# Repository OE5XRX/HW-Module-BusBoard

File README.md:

# HW-Module-BusBoard

## License

This project is licensed under [CERN-OHL-S-2.0](https://choosealicense.com/licenses/cern-ohl-s-2.0/).

## Badges

<br>
<br>
<br>
<br>
<br>

## Contact

OE5XRX Amateur Radio Club<br>
🌐 https://oe5xrx.org<br>
✉️ info@oe5xrx.org<br>

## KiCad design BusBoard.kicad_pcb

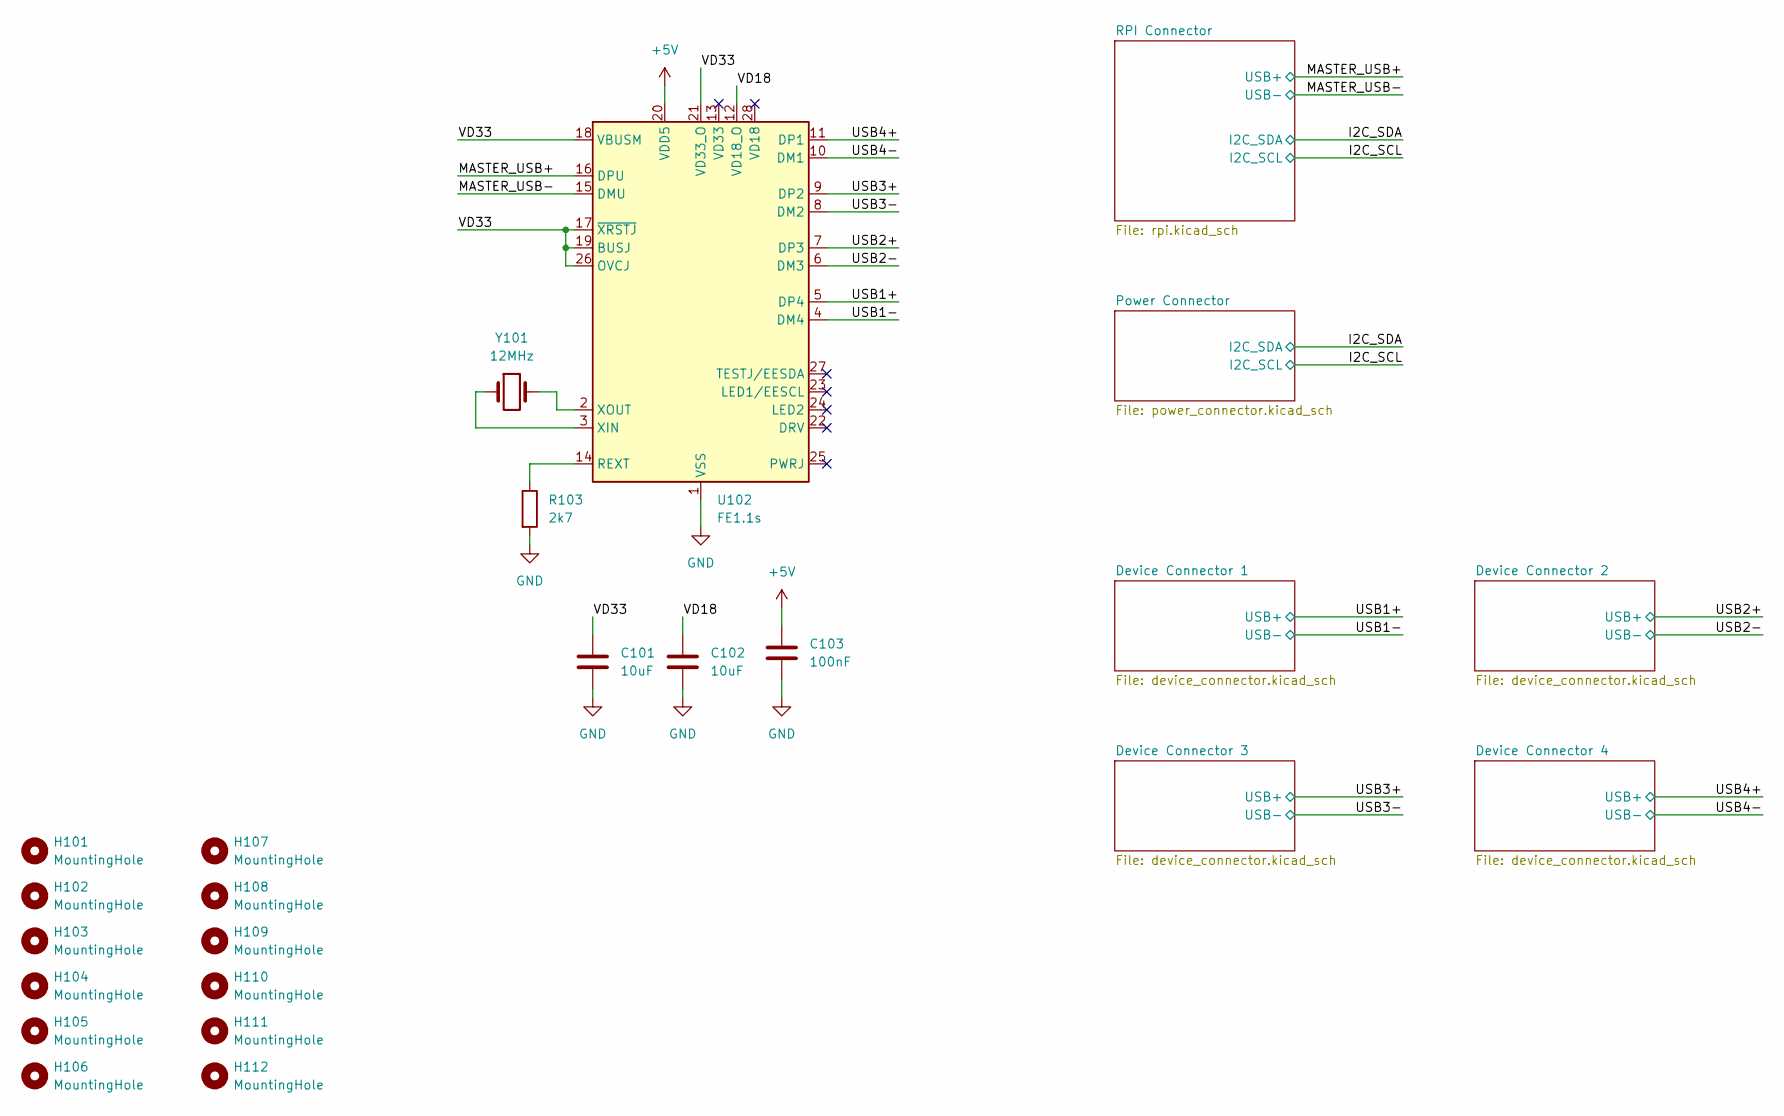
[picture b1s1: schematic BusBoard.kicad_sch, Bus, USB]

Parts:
C101, C102: 10uF; C_0805_2012Metric; LCSC C13585
C103: 100nF; C_0805_2012Metric; LCSC C28233
H101, H102, H103, H104, H105, H106, H107, H108, H109, H110, H111, H112: MountingHole; MountingHole_3.2mm_M3
R103: 2k7; R_0805_2012Metric; LCSC C352230
U102: FE1.1s; SSOP-28_3.9x9.9mm_P0.635mm; LCSC C6706491
Y101: 12MHz; M49S-SMD; LCSC C2983432

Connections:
+5V: C103.1, U102.20 (VDD5); also elsewhere on the board
/MASTER_USB+: U102.16 (DPU); also elsewhere on the board
/MASTER_USB-: U102.15 (DMU); also elsewhere on the board
/USB1+: U102.5 (DP4); also elsewhere on the board
/USB1-: U102.4 (DM4); also elsewhere on the board
/USB2+: U102.7 (DP3); also elsewhere on the board
/USB2-: U102.6 (DM3); also elsewhere on the board
/USB3+: U102.9 (DP2); also elsewhere on the board
/USB3-: U102.8 (DM2); also elsewhere on the board
/USB4+: U102.11 (DP1); also elsewhere on the board
/USB4-: U102.10 (DM1); also elsewhere on the board
/VD18: C102.1, U102.12 (VD18_O)
/VD33: C101.1, U102.17 (~XRSTJ), U102.18 (VBUSM), U102.19 (BUSJ), U102.21 (VD33_O), U102.26 (OVCJ)
GND: C101.2, C102.2, C103.2, R103.2, U102.1 (VSS); also elsewhere on the board
unnamed: R103.1, U102.14 (REXT)
unnamed: U102.3 (XIN), Y101.1
unnamed: U102.2 (XOUT), Y101.2

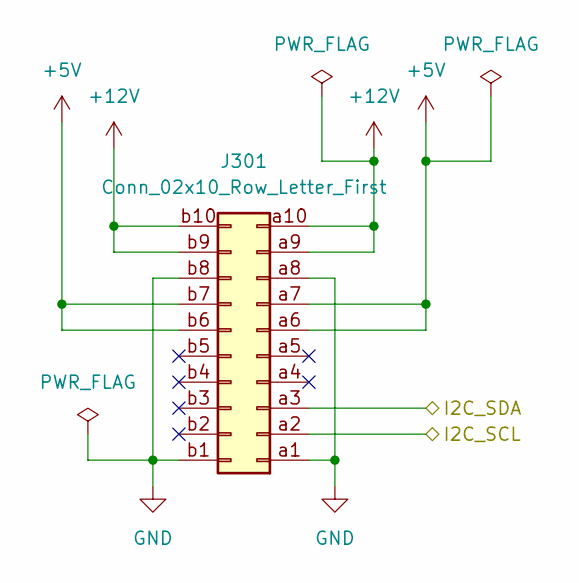
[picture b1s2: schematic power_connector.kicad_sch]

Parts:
J301: Conn_02x10_Row_Letter_First; PCN10-20P-2.54DSA; MOUSER 798-PCN1020P254DSA72

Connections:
+5V: J301.a6, J301.a7, J301.b6, J301.b7; also elsewhere on the board
+12V: J301.a9, J301.a10, J301.b9, J301.b10; also elsewhere on the board
/I2C_SCL: J301.a2; also elsewhere on the board
/I2C_SDA: J301.a3; also elsewhere on the board
GND: J301.a1, J301.a8, J301.b1, J301.b8; also elsewhere on the board

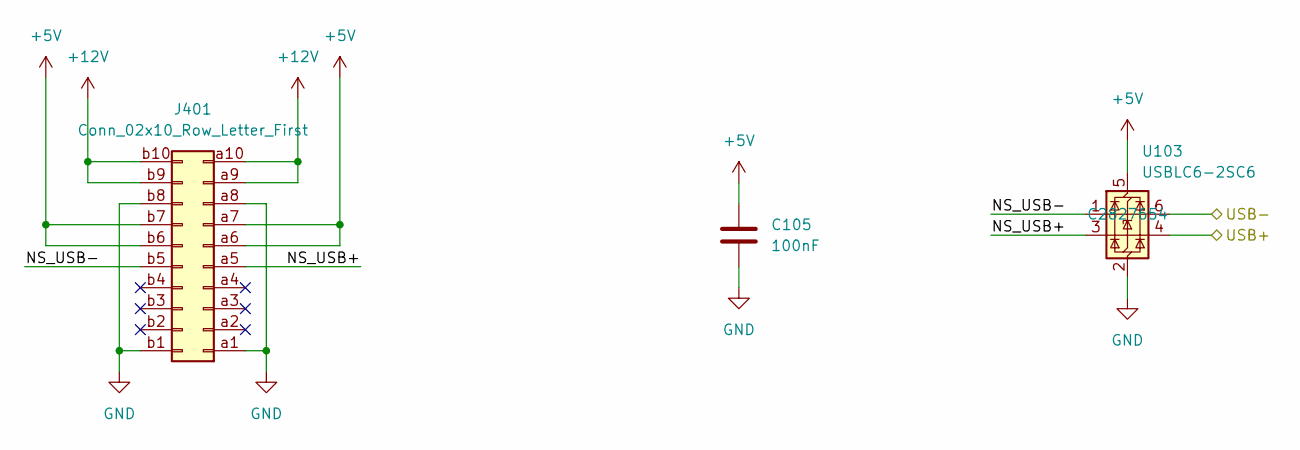
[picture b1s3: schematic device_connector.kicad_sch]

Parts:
C105: 100nF; C_0805_2012Metric; LCSC C28233
J401: Conn_02x10_Row_Letter_First; PCN10-20P-2.54DSA; MOUSER 798-PCN1020P254DSA72
U103: USBLC6-2SC6; SOT-23-6; LCSC C2827654

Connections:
+5V: C105.1, J401.a6, J401.a7, J401.b6, J401.b7, U103.5 (VBUS); also elsewhere on the board
+12V: J401.a9, J401.a10, J401.b9, J401.b10; also elsewhere on the board
/Device Connector 1/NS_USB+: J401.a5, U103.3 (I/O2)
/Device Connector 1/NS_USB-: J401.b5, U103.1 (I/O1)
/USB1+: U103.4 (I/O2); also elsewhere on the board
/USB1-: U103.6 (I/O1); also elsewhere on the board
GND: C105.2, J401.a1, J401.a8, J401.b1, J401.b8, U103.2 (GND); also elsewhere on the board

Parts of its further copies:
C106, C107, C108: 100nF; C_0805_2012Metric; LCSC C28233
J501, J601, J701: Conn_02x10_Row_Letter_First; PCN10-20P-2.54DSA; MOUSER 798-PCN1020P254DSA72
U104, U105, U106: USBLC6-2SC6; SOT-23-6; LCSC C2827654

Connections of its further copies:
+5V: C106.1, C107.1, C108.1, J501.a6, J501.a7, J501.b6, J501.b7, J601.a6, J601.a7, J601.b6, J601.b7, J701.a6, J701.a7, J701.b6, J701.b7, U104.5 (VBUS), U105.5 (VBUS), U106.5 (VBUS); also elsewhere on the board
+12V: J501.a9, J501.a10, J501.b9, J501.b10, J601.a9, J601.a10, J601.b9, J601.b10, J701.a9, J701.a10, J701.b9, J701.b10; also elsewhere on the board
/Device Connector 2/NS_USB+: J501.a5, U104.3 (I/O2)
/Device Connector 2/NS_USB-: J501.b5, U104.1 (I/O1)
/Device Connector 3/NS_USB+: J601.a5, U105.3 (I/O2)
/Device Connector 3/NS_USB-: J601.b5, U105.1 (I/O1)
/Device Connector 4/NS_USB+: J701.a5, U106.3 (I/O2)
/Device Connector 4/NS_USB-: J701.b5, U106.1 (I/O1)
/USB2+: U104.4 (I/O2); also elsewhere on the board
/USB2-: U104.6 (I/O1); also elsewhere on the board
/USB3+: U105.4 (I/O2); also elsewhere on the board
/USB3-: U105.6 (I/O1); also elsewhere on the board
/USB4+: U106.4 (I/O2); also elsewhere on the board
/USB4-: U106.6 (I/O1); also elsewhere on the board
GND: C106.2, C107.2, C108.2, J501.a1, J501.a8, J501.b1, J501.b8, J601.a1, J601.a8, J601.b1, J601.b8, J701.a1, J701.a8, J701.b1, J701.b8, U104.2 (GND), U105.2 (GND), U106.2 (GND); also elsewhere on the board

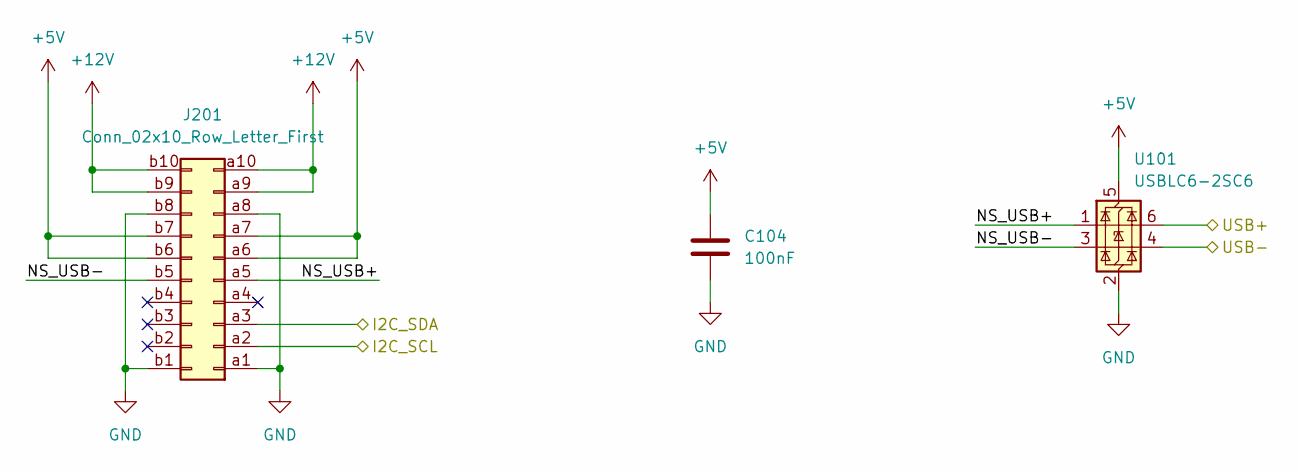
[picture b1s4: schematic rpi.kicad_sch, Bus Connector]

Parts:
C104: 100nF; C_0805_2012Metric; LCSC C28233
J201: Conn_02x10_Row_Letter_First; PCN10-20P-2.54DSA; MOUSER 798-PCN1020P254DSA72
U101: USBLC6-2SC6; SOT-23-6; LCSC C2827654

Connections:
+5V: C104.1, J201.a6, J201.a7, J201.b6, J201.b7, U101.5 (VBUS); also elsewhere on the board
+12V: J201.a9, J201.a10, J201.b9, J201.b10; also elsewhere on the board
/I2C_SCL: J201.a2; also elsewhere on the board
/I2C_SDA: J201.a3; also elsewhere on the board
/MASTER_USB+: U101.6 (I/O1); also elsewhere on the board
/MASTER_USB-: U101.4 (I/O2); also elsewhere on the board
/RPI Connector/NS_USB+: J201.a5, U101.1 (I/O1)
/RPI Connector/NS_USB-: J201.b5, U101.3 (I/O2)
GND: C104.2, J201.a1, J201.a8, J201.b1, J201.b8, U101.2 (GND); also elsewhere on the board

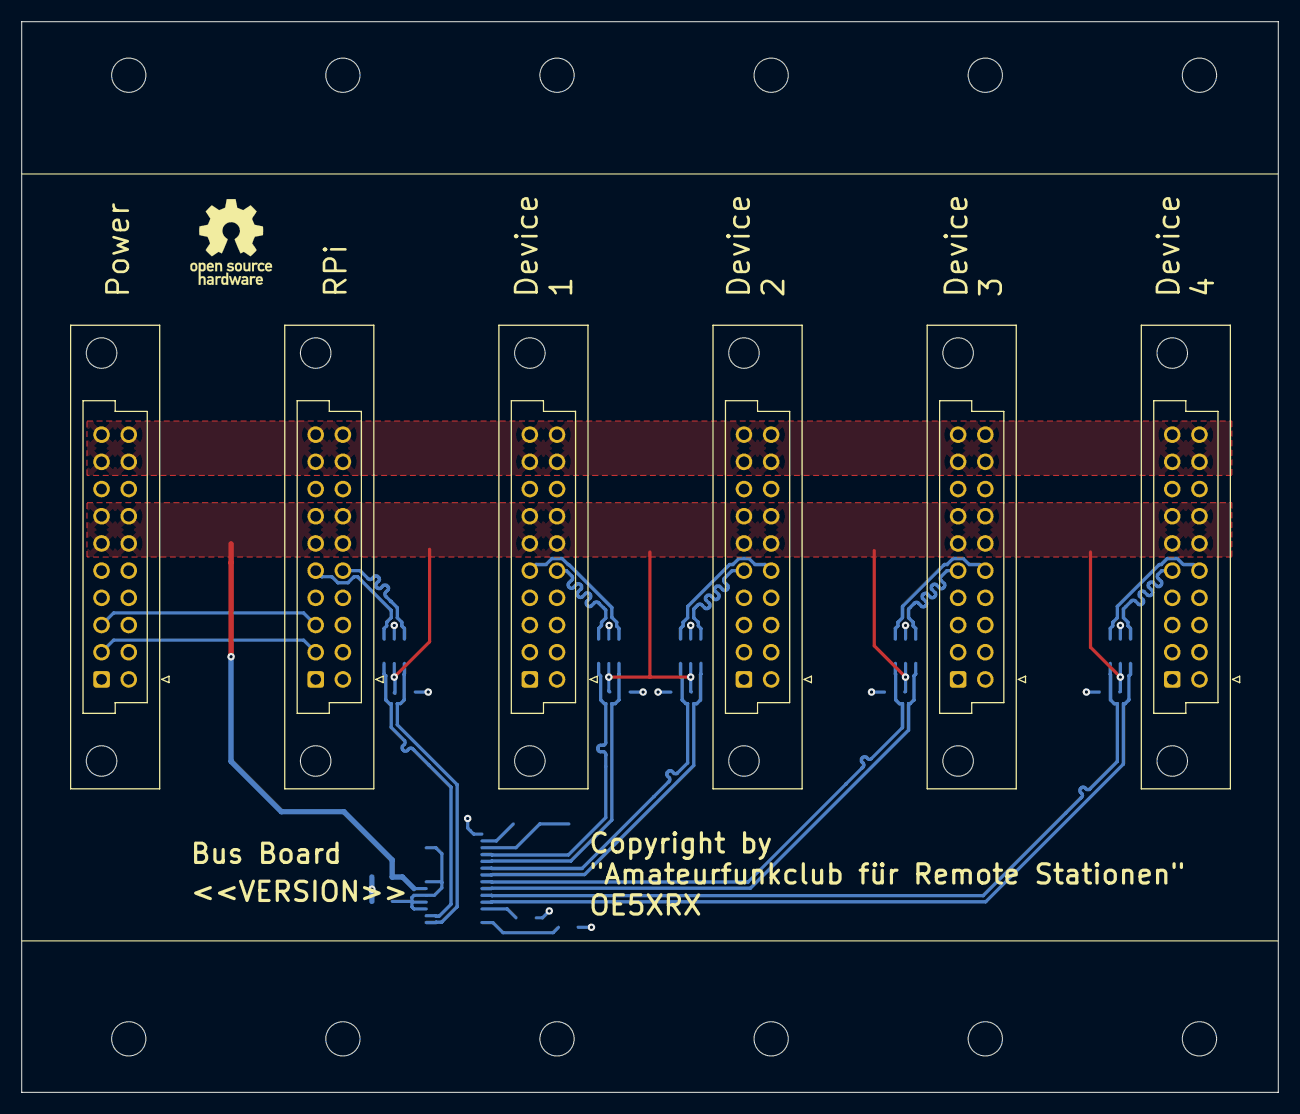
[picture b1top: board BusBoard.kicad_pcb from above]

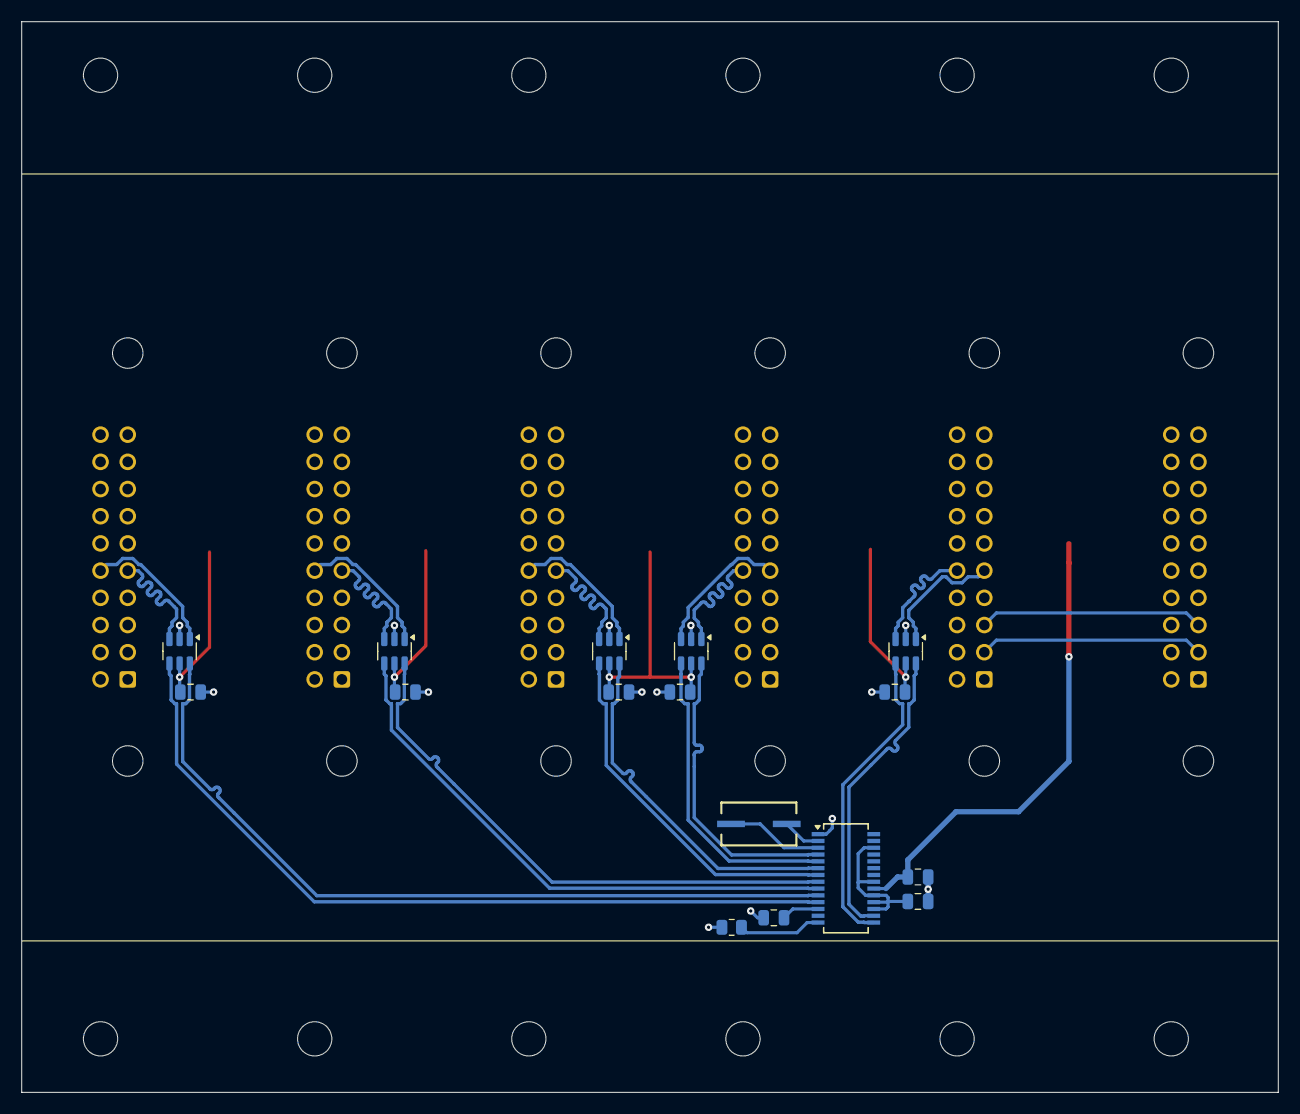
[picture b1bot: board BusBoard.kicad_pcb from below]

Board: 4 copper layers, 117.4 x 100.0 mm, 34 parts (16 on the bottom side), 30 nets.

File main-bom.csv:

Row,Description,Part,References,Value,Footprint,Quantity Per PCB,Status,Datasheet,LCSC,MOUSER
1,Unpolarized capacitor,C,C103 C104 C105 C106 C107 C108,100nF,C_0805_2012Metric,6, ,~,C28233,
2,Unpolarized capacitor,C,C101 C102,10uF,C_0805_2012Metric,2, ,~,C13585,
3,"Generic connector, double row, 02x10, row letter first pin numbering scheme (pin number consists of a letter for the row and a number for the pin index in this row. a1, ..., aN; b1, ..., bN), script generated (kicad-library-utils/schlib/autogen/connector/)",Conn_02x10_Row_Letter_First,J201 J301 J401 J501 J601 J701,Conn_02x10_Row_Letter_First,PCN10-20P-2.54DSA,6, ,~,,798-PCN1020P254DSA72
4,Resistor,R,R103,2k7,R_0805_2012Metric,1, ,~,C352230,
5,"USB 2.0 High Speed 4-Port Hub Controller, SSOP-28",FE1.1s,U102,FE1.1s,SSOP-28_3.9x9.9mm_P0.635mm,1, ,https://cdn-shop.adafruit.com/product-files/2991/FE1.1s+Data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,C6706491,
6,"Very low capacitance ESD protection diode, 2 data-line, SOT-23-6",USBLC6-2SC6,U101 U103 U104 U105 U106,USBLC6-2SC6,SOT-23-6,5, ,https://www.st.com/resource/en/datasheet/usblc6-2.pdf,C2827654,
7,Two pin crystal,Crystal,Y101,12MHz,M49S-SMD,1, ,~,C2983432,

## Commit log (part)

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2025-08-27 setup new project
2025-08-27 fix path
2025-09-05 🔄 synced local '.github/workflows/create-debug-docs.yaml' with remote '.github/workflows/create-debug-docs.yaml'
2025-09-05 🔄 created local 'Gemfile' from remote 'Gemfile'
2025-09-05 🔄 created local 'doc/favicon.ico' from remote 'doc/favicon.ico'
2025-09-05 🔄 created local 'doc/_config.yml' from remote 'doc/_config.yml'
2025-09-05 Initial gh-pages commit
2025-09-05 Deploying to gh-pages from @ OE5XRX/HW-Module-BusBoard@e1a87b12e2d77169ac47c8977f8651aeaf01f613 🚀
2026-05-12 refactor(ci): replace workflows with HW-Module-CI thin wrappers
2026-05-12 chore(ci): delete files now provided by HW-Module-CI
2026-05-12 feat(docs): migrate index.md to Jekyll Liquid for output paths
2026-05-12 chore: ignore CI-generated doc/_data/project.yml
2026-05-12 rename(kicad): main.kicad_* → BusBoard.kicad_*
    Distinguishable KiCad window titles on the desktop. The composite action
    in HW-Module-CI auto-detects the project name from the basename of
    *.kicad_pro, so CI behaviour is identical before and after — only the
    artefact filenames change (main-bom.html → BusBoard-bom.html etc.),
    which doc/index.md already routes through {{ site.data.project.name }}.
    Internal references updated:
2026-05-12 Deploying to gh-pages from @ OE5XRX/HW-Module-BusBoard@4ceeb46072880124e3b0e307cc13ac4e7f63df29 🚀
2026-05-12 Deploying to gh-pages from @ OE5XRX/HW-Module-BusBoard@e771a67ccc9f595509b72fd658fea01775678b3a 🚀
2026-05-12 docs: rewrite Bus index.md with overview, block-diagram, full 20-pin pinout
    Adds:
    - 1-sentence description front-matter
    - Übersicht highlighting the role as backplane (power distribution +
    4-port USB hub for CM4 → slots)
    - Mermaid block diagram showing the topology (PowerBoard, CM4, 4 slots
    meeting on the BusBoard with FE1.1s in the middle)
2026-05-12 Deploying to gh-pages from @ OE5XRX/HW-Module-BusBoard@3ed2cb26e77b58a0b97293518ccf2a39ccb1c6bb 🚀
2026-05-13 fix(docs): adressiere 4 Copilot-Review-Findings auf PR #5
    1. Mermaid: 'BB' wurde sowohl als Subgraph-ID als auch als Node-Ziel
    verwendet (PB → BB / CM4 → BB UND subgraph BB [...]). Umbenannt:
    die Hub-Node heisst jetzt 'Hub', der BusBoard-Subgraph bleibt 'BB'.
    2. Pin-Belegung-Überschrift war widersprüchlich: 'identisch auf allen
    Konnektoren' obwohl Signale sich je Rolle unterscheiden. Neu:
    'Power identisch, Signale rollenspezifisch'.
2026-05-13 Deploying to gh-pages from @ OE5XRX/HW-Module-BusBoard@b67e1a79b2e4219429d4735f8f274fec3957488d 🚀
2026-05-15 Deploying to gh-pages from @ OE5XRX/HW-Module-BusBoard@ab215aa1cb0ed2eb4662c0229cc22239bb87469c 🚀
2026-05-15 Deploying to gh-pages from @ OE5XRX/HW-Module-BusBoard@327071cc27a2d02b1bffbfe04a3f841f92f000c5 🚀

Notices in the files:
BusBoard.kicad_pcb:
Copyright by
{dblquote}Amateurfunkclub für Remote Stationen{dblquote}
README.md:
License: CERN-OHL-S
